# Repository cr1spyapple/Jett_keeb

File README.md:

# JETT
<b> A wired 56 key split keyboard powered by RP2040 microcontrollers.
</b>

3D render:

Final build:

After creating the GOATPad i decided to take up a slightly more challenging twist to that project. This time a full split keyboard, which taught me how to panelize PCBs and make two MCU's communicate together.

  ### Specs
- Raspberry Pico microcontroller
- 56 keys
- MX Brown switches
- USB Type-C connectivity
- 3D Printed Case

## Schematic
### Left

### Right

## PCB

## Case

## Bill of Materials

|Name                               |Purpose                          |Quantity|Total Cost (USD)|Link                                                                                                                                        |Distributor|
|-----------------------------------|---------------------------------|--------|----------------|--------------------|-----------|
|M2 Heat inserts                    |Screw holes in case              |1       |1.95            |https://www.aliexpress.com/item/1005007640664497.html?mp=1&pdp_ext_f=%7B%22cart2PdpParams%22%3A%7B%22pdpBusinessMode%22%3A%22retail%22%7D%7D|Aliexpress |
|M2 Screws                          |Mounting PCB to case             |1       |1.35            |https://www.aliexpress.com/item/4000026780118.html?mp=1&pdp_ext_f=%7B%22cart2PdpParams%22%3A%7B%22pdpBusinessMode%22%3A%22retail%22%7D%7D   |Aliexpress |
|3.5mm PJ-320D audio jack (10PCS)   |Port for TRRS cable              |        |1.20            |https://www.aliexpress.com/item/4000661908135.html                                                                                          |Aliexpress |
|1N5819WS SOD-323 Diodes (100PCS)   |Diodes for key matrix            |        |1.64            |https://www.aliexpress.com/item/1005006216984245.html                                                                                       |Aliexpress |
|Male-to-Male TRRS cable            |For MCU's to share power and data|1       |2.50            |https://www.aliexpress.com/item/1005008288720867.html                                                                                       |Aliexpress |
|Black XDA Profile keycaps (64PCS)  |Key caps                         |        |15.06           |https://www.aliexpress.com/item/1005011932744770.html?mp=1                                                                                  |Aliexpress |
|MX style Brown key switches (80PCS)|Key switches                     |        |6.91            |https://www.aliexpress.com/item/1005011838889689.html                                                                                       |Aliexpress |
|Raspberry Pico                     |Microcontroller                  |2       |4.55            |https://www.aliexpress.com/item/1005005617180169.html                                                                                       |Aliexpress |
|PCB                                |Keyboard PCB                     |5       |22.90           |                                                                                                                                            |JLCPCB     |
|  | TOTAL |  | 58.06 |  |  |

*Not including shipping and tax

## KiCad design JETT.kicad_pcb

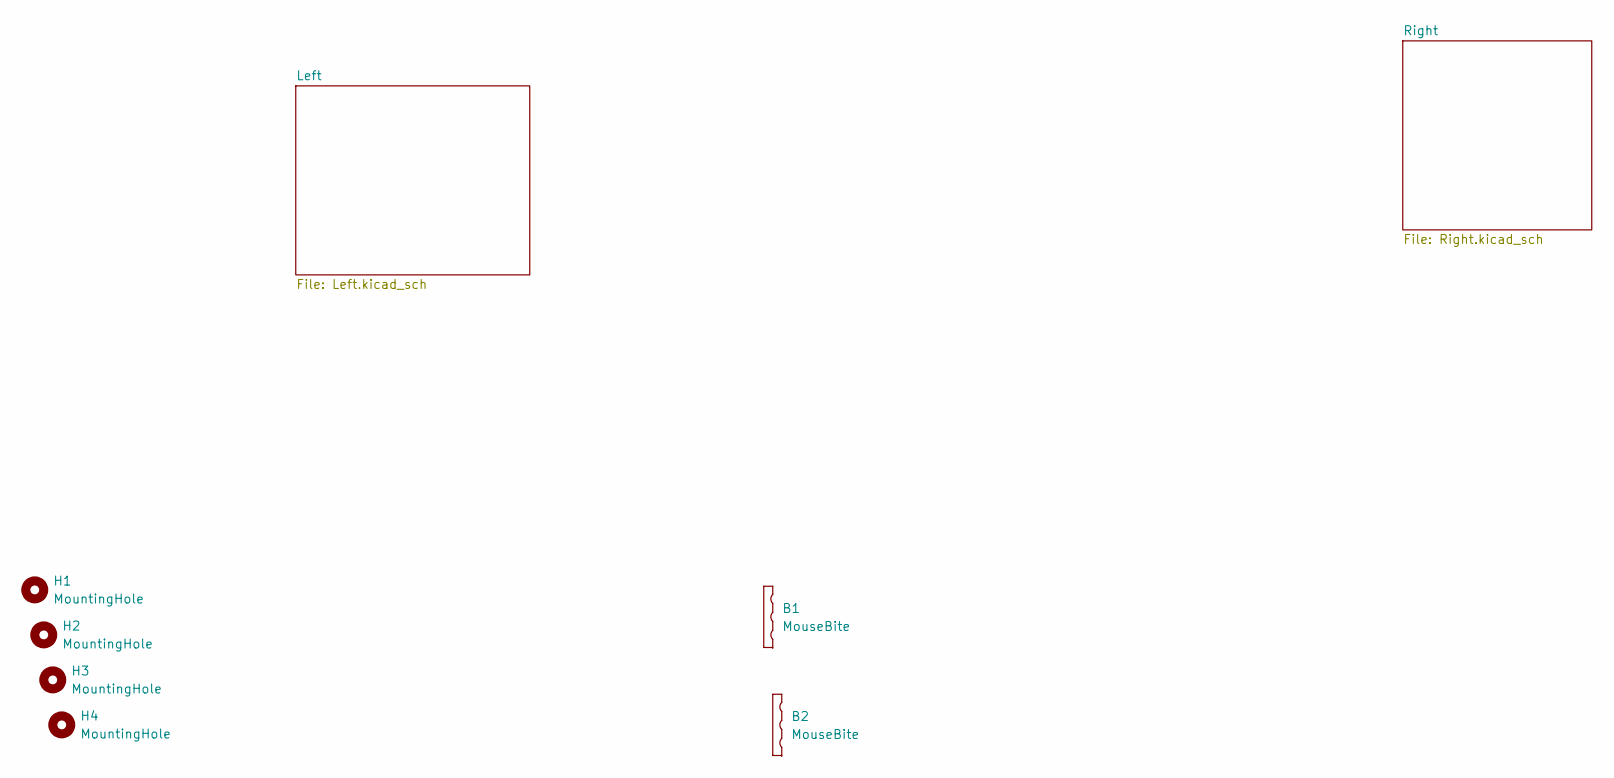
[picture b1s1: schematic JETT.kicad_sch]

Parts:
B1, B2: MouseBite; mouse-bite-2mm-slot
H1, H2, H3, H4: MountingHole; MountingHole_2.2mm_M2

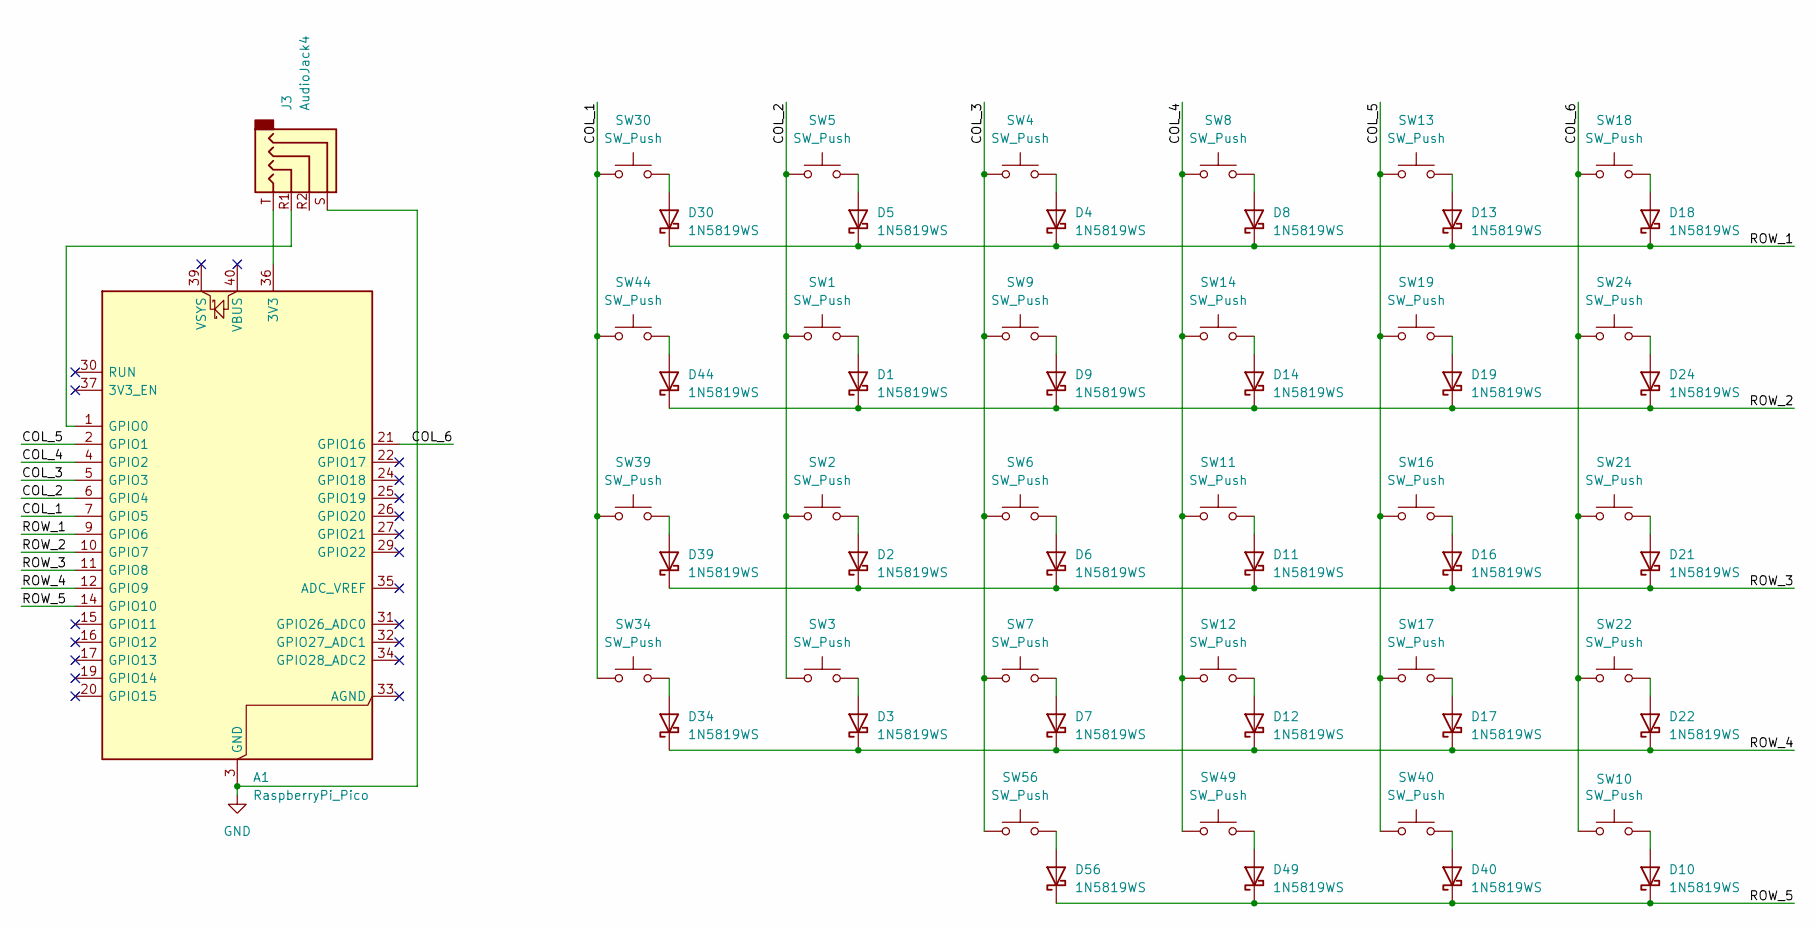
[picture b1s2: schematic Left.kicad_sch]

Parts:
A1: RaspberryPi_Pico; RaspberryPi_Pico_Common_SMD
D1, D2, D3, D4, D5, D6, D7, D8, D9, D10, D11, D12, D13, D14, D16, D17, D18, D19, D21, D22, D24, D30, D34, D39, D40, D44, D49, D56: 1N5819WS; D_SOD-323_HandSoldering
J3: AudioJack4; Jack_3.5mm_PJ320D_Horizontal
SW1, SW2, SW3, SW4, SW5, SW6, SW7, SW8, SW9, SW10, SW11, SW12, SW13, SW14, SW16, SW17, SW18, SW19, SW21, SW22, SW24, SW30, SW34, SW39, SW40, SW44, SW49, SW56: SW_Push; SW_Cherry_MX_1.00u_PCB

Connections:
/Left/COL_1: A1.7 (GPIO5), SW30.1, SW34.1, SW39.1, SW44.1
/Left/COL_2: A1.6 (GPIO4), SW1.1, SW2.1, SW3.1, SW5.1
/Left/COL_3: A1.5 (GPIO3), SW4.1, SW6.1, SW7.1, SW9.1, SW56.1
/Left/COL_4: A1.4 (GPIO2), SW8.1, SW11.1, SW12.1, SW14.1, SW49.1
/Left/COL_5: A1.2 (GPIO1), SW13.1, SW16.1, SW17.1, SW19.1, SW40.1
/Left/COL_6: A1.21 (GPIO16), SW10.1, SW18.1, SW21.1, SW22.1, SW24.1
/Left/ROW_1: A1.9 (GPIO6), D4.1 (K), D5.1 (K), D8.1 (K), D13.1 (K), D18.1 (K), D30.1 (K)
/Left/ROW_2: A1.10 (GPIO7), D1.1 (K), D9.1 (K), D14.1 (K), D19.1 (K), D24.1 (K), D44.1 (K)
/Left/ROW_3: A1.11 (GPIO8), D2.1 (K), D6.1 (K), D11.1 (K), D16.1 (K), D21.1 (K), D39.1 (K)
/Left/ROW_4: A1.12 (GPIO9), D3.1 (K), D7.1 (K), D12.1 (K), D17.1 (K), D22.1 (K), D34.1 (K)
/Left/ROW_5: A1.14 (GPIO10), D10.1 (K), D40.1 (K), D49.1 (K), D56.1 (K)
GND: A1.3 (GND), A1.8 (GND), A1.13 (GND), A1.18 (GND), A1.23 (GND), A1.28 (GND), A1.38 (GND), J3.S; also elsewhere on the board
unnamed: A1.36 (3V3), J3.T
unnamed: A1.1 (GPIO0), J3.R1
unnamed: D1.2 (A), SW1.2
unnamed: D2.2 (A), SW2.2
unnamed: D3.2 (A), SW3.2
unnamed: D4.2 (A), SW4.2
unnamed: D5.2 (A), SW5.2
unnamed: D6.2 (A), SW6.2
unnamed: D7.2 (A), SW7.2
unnamed: D8.2 (A), SW8.2
unnamed: D9.2 (A), SW9.2
unnamed: D10.2 (A), SW10.2
unnamed: D11.2 (A), SW11.2
unnamed: D12.2 (A), SW12.2
unnamed: D13.2 (A), SW13.2
unnamed: D14.2 (A), SW14.2
unnamed: D16.2 (A), SW16.2
unnamed: D17.2 (A), SW17.2
unnamed: D18.2 (A), SW18.2
unnamed: D19.2 (A), SW19.2
unnamed: D21.2 (A), SW21.2
unnamed: D22.2 (A), SW22.2
unnamed: D24.2 (A), SW24.2
unnamed: D30.2 (A), SW30.2
unnamed: D34.2 (A), SW34.2
unnamed: D39.2 (A), SW39.2
unnamed: D40.2 (A), SW40.2
unnamed: D44.2 (A), SW44.2
unnamed: D49.2 (A), SW49.2
unnamed: D56.2 (A), SW56.2

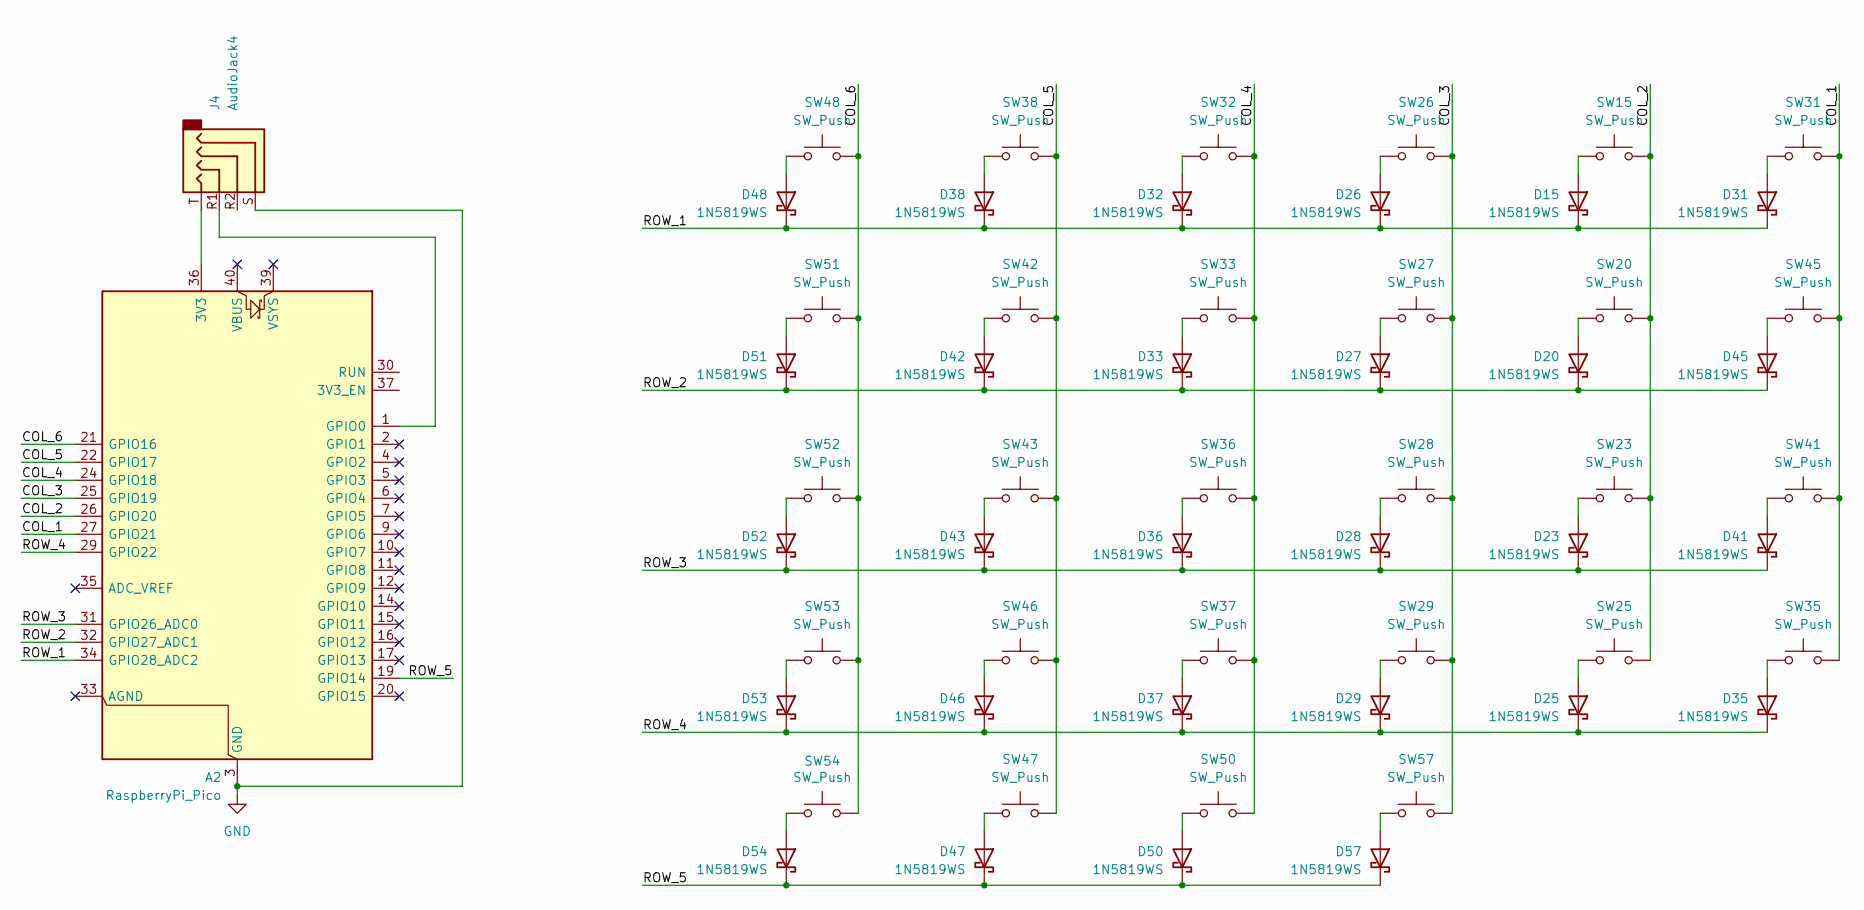
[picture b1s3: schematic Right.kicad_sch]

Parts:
A2: RaspberryPi_Pico; RaspberryPi_Pico_Common_SMD
D15, D20, D23, D25, D26, D27, D28, D29, D31, D32, D33, D35, D36, D37, D38, D41, D42, D43, D45, D46, D47, D48, D50, D51, D52, D53, D54, D57: 1N5819WS; D_SOD-323_HandSoldering
J4: AudioJack4; Jack_3.5mm_PJ320D_Horizontal
SW15, SW20, SW23, SW25, SW26, SW27, SW28, SW29, SW31, SW32, SW33, SW35, SW36, SW37, SW38, SW41, SW42, SW43, SW45, SW46, SW47, SW48, SW50, SW51, SW52, SW53, SW54, SW57: SW_Push; SW_Cherry_MX_1.00u_PCB

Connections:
/Right/COL_1: A2.27 (GPIO21), SW31.1, SW35.1, SW41.1, SW45.1
/Right/COL_2: A2.26 (GPIO20), SW15.1, SW20.1, SW23.1, SW25.1
/Right/COL_3: A2.25 (GPIO19), SW26.1, SW27.1, SW28.1, SW29.1, SW57.1
/Right/COL_4: A2.24 (GPIO18), SW32.1, SW33.1, SW36.1, SW37.1, SW50.1
/Right/COL_5: A2.22 (GPIO17), SW38.1, SW42.1, SW43.1, SW46.1, SW47.1
/Right/COL_6: A2.21 (GPIO16), SW48.1, SW51.1, SW52.1, SW53.1, SW54.1
/Right/ROW_1: A2.34 (GPIO28_ADC2), D15.1 (K), D26.1 (K), D31.1 (K), D32.1 (K), D38.1 (K), D48.1 (K)
/Right/ROW_2: A2.32 (GPIO27_ADC1), D20.1 (K), D27.1 (K), D33.1 (K), D42.1 (K), D45.1 (K), D51.1 (K)
/Right/ROW_3: A2.31 (GPIO26_ADC0), D23.1 (K), D28.1 (K), D36.1 (K), D41.1 (K), D43.1 (K), D52.1 (K)
/Right/ROW_4: A2.29 (GPIO22), D25.1 (K), D29.1 (K), D35.1 (K), D37.1 (K), D46.1 (K), D53.1 (K)
/Right/ROW_5: A2.19 (GPIO14), D47.1 (K), D50.1 (K), D54.1 (K), D57.1 (K)
GND: A2.3 (GND), A2.8 (GND), A2.13 (GND), A2.18 (GND), A2.23 (GND), A2.28 (GND), A2.38 (GND), J4.S; also elsewhere on the board
unnamed: A2.36 (3V3), J4.T
unnamed: A2.1 (GPIO0), J4.R1
unnamed: D15.2 (A), SW15.2
unnamed: D20.2 (A), SW20.2
unnamed: D23.2 (A), SW23.2
unnamed: D25.2 (A), SW25.2
unnamed: D26.2 (A), SW26.2
unnamed: D27.2 (A), SW27.2
unnamed: D28.2 (A), SW28.2
unnamed: D29.2 (A), SW29.2
unnamed: D31.2 (A), SW31.2
unnamed: D32.2 (A), SW32.2
unnamed: D33.2 (A), SW33.2
unnamed: D35.2 (A), SW35.2
unnamed: D36.2 (A), SW36.2
unnamed: D37.2 (A), SW37.2
unnamed: D38.2 (A), SW38.2
unnamed: D41.2 (A), SW41.2
unnamed: D42.2 (A), SW42.2
unnamed: D43.2 (A), SW43.2
unnamed: D45.2 (A), SW45.2
unnamed: D46.2 (A), SW46.2
unnamed: D47.2 (A), SW47.2
unnamed: D48.2 (A), SW48.2
unnamed: D50.2 (A), SW50.2
unnamed: D51.2 (A), SW51.2
unnamed: D52.2 (A), SW52.2
unnamed: D53.2 (A), SW53.2
unnamed: D54.2 (A), SW54.2
unnamed: D57.2 (A), SW57.2

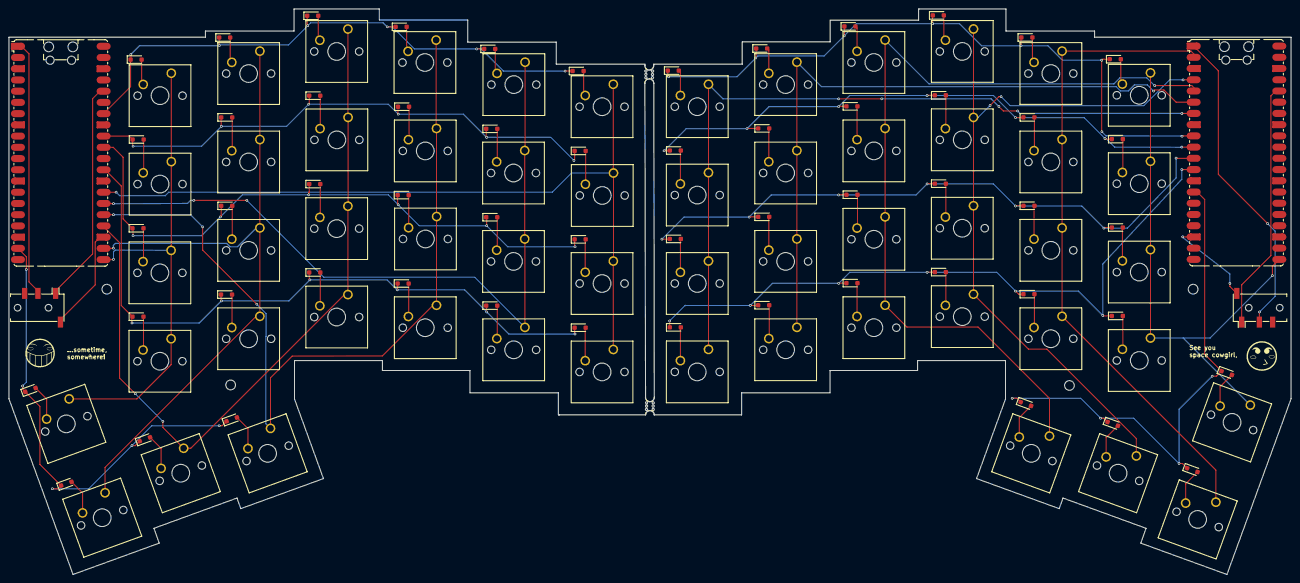
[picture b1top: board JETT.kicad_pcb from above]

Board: 2 copper layers, 290.1 x 128.0 mm, 122 parts (0 on the bottom side), 83 nets.
